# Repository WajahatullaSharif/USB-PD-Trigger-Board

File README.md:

# **USB C PD Trigger Board**
- The USB PD Trigger Board is based on **AP33771C USB PD3.1 ERP sink controller** from Diodes Incorporated. 
- This board negotiates required **voltages (5V/9V/12V/15V/20V/28V) and current (0 to 5A max)** profiles requested using the respective jumpers with the Type C Power Source (typically charger/adaptor). 
- It includes safety features like Over/Under Voltage, Over Current, Over Temperature Protections along with IN/OUT isolation. The board is also immune to ± 30 kV Air/Contact ESD dicharge (IEC 61000-4-2)

# Kicad 9 files
- The hardware is designed on KiCad 9.
## Schematic

## Layout

## 3D Model

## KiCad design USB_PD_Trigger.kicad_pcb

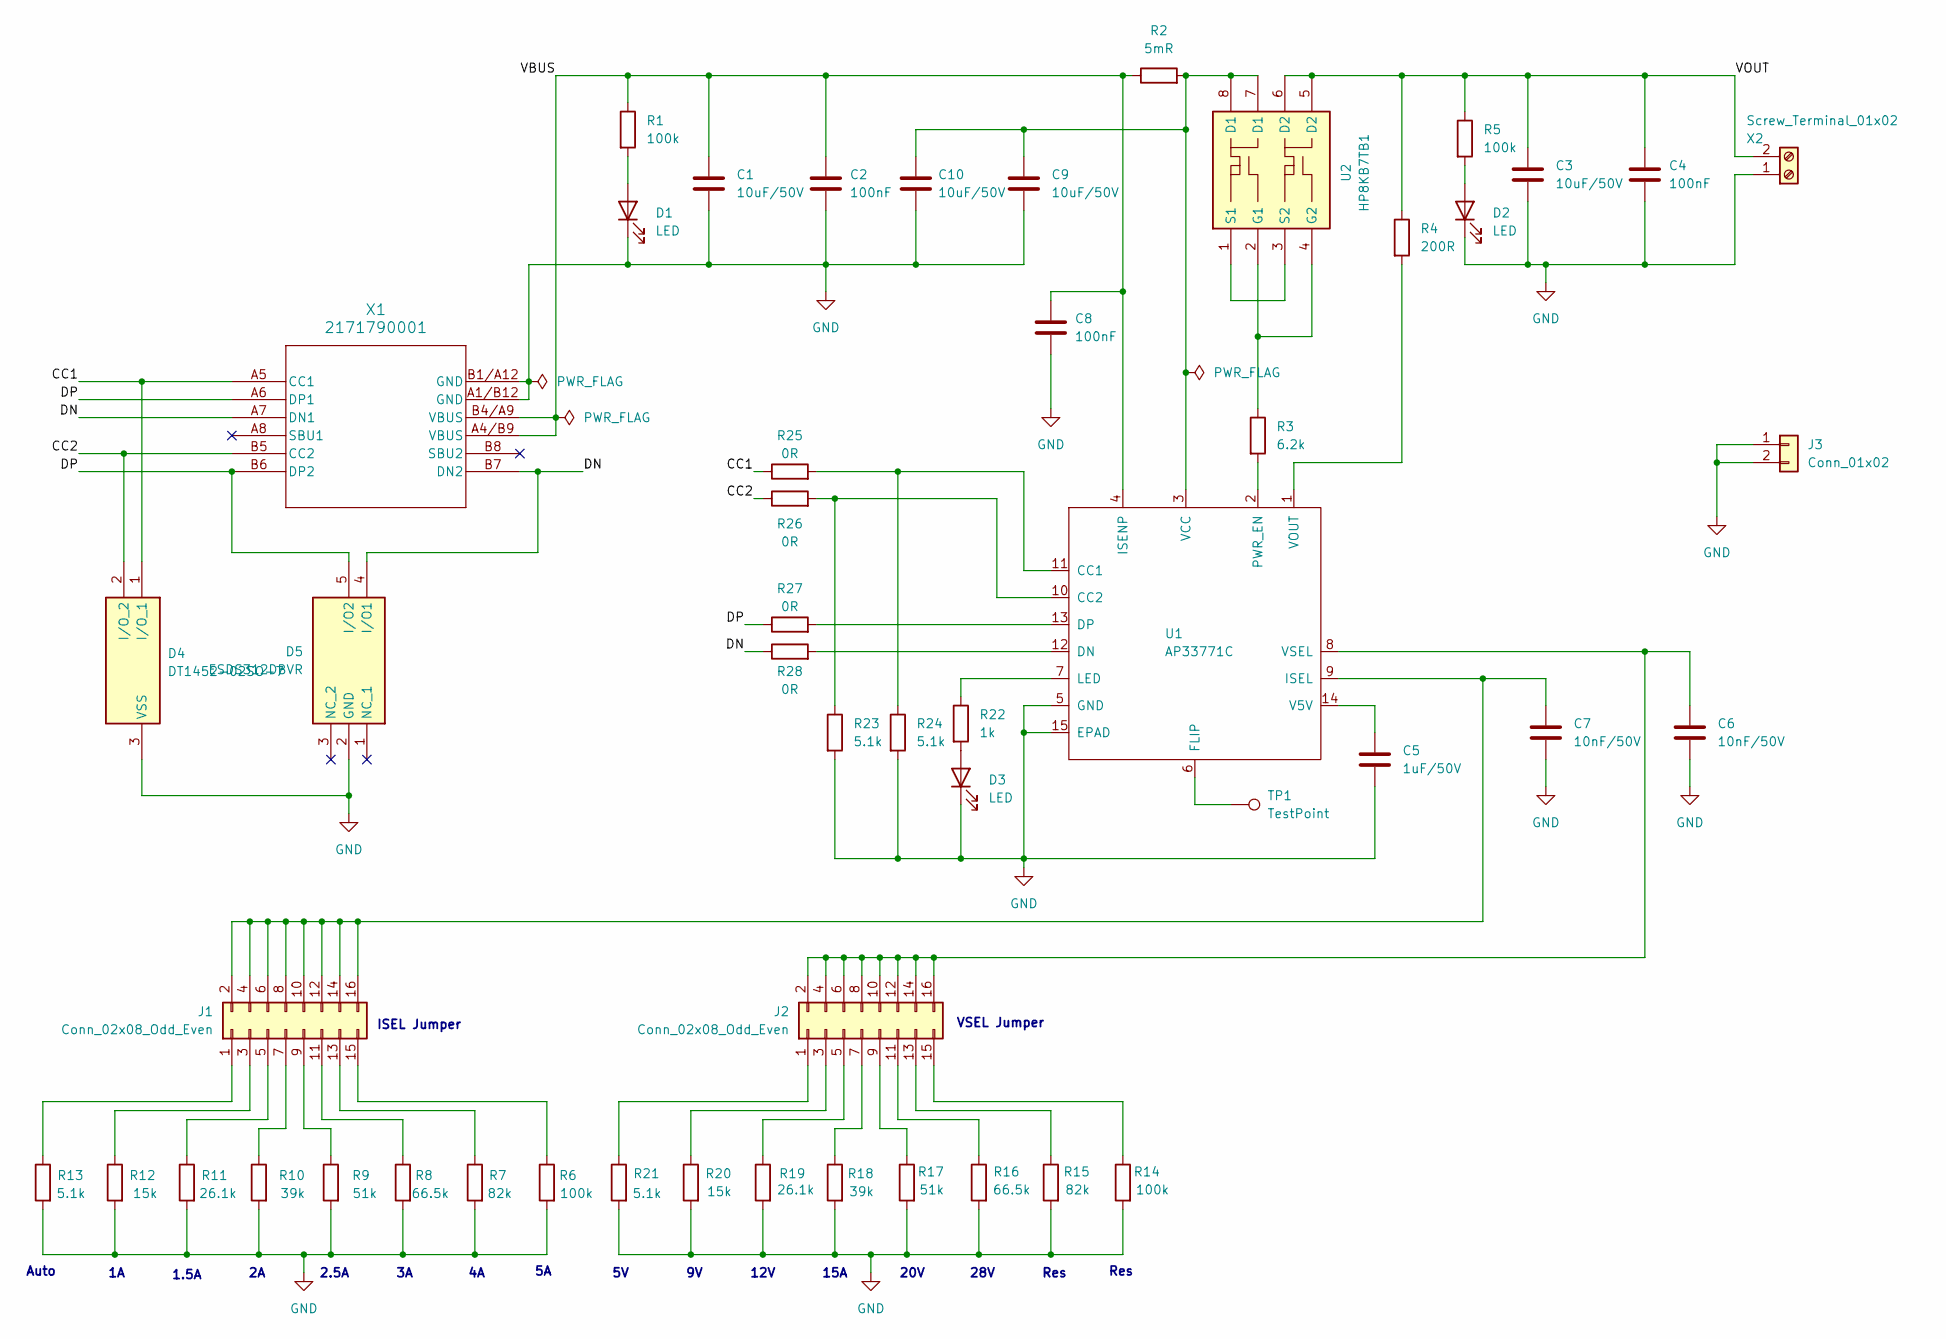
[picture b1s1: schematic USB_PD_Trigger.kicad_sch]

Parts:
C1, C3, C9, C10: 10uF/50V; C_1206_3216Metric; Manufacturer_Part_Number CL31B106KBHNNNE
C2, C4, C8: 100nF; C_0603_1608Metric; Manufacturer_Part_Number GRM188R71H104KA93D
C5: 1uF/50V; C_0603_1608Metric; Manufacturer_Part_Number CC0603KRX7R9BB105
C6, C7: 10nF/50V; C_0603_1608Metric; Manufacturer_Part_Number CC0603KRX7R9BB103
D1, D2, D3: LED; LED_0805_2012Metric
D4: DT1452-02SO-7; Mouser Part Number 621-DT1452-02SO-7
D5: ESDS312DBVR; Mouser Part Number 595-ESDS312DBVR
J1, J2: Conn_02x08_Odd_Even; PinHeader_2x08_P2.54mm_Vertical
J3: Conn_01x02; PinHeader_1x02_P2.54mm_Vertical
R1, R5, R6, R14: 100k; R_0603_1608Metric
R2: 5mR; R_1206_3216Metric
R3: 6.2k; R_0603_1608Metric
R4: 200R; R_0603_1608Metric
R7, R15: 82k; R_0603_1608Metric
R8, R16: 66.5k; R_0603_1608Metric
R9, R17: 51k; R_0603_1608Metric
R10, R18: 39k; R_0603_1608Metric
R11, R19: 26.1k; R_0603_1608Metric
R12, R20: 15k; R_0603_1608Metric
R13, R21, R23, R24: 5.1k; R_0603_1608Metric
R22: 1k; R_0603_1608Metric
R25, R26, R27, R28: 0R; R_0603_1608Metric
TP1: TestPoint; TestPoint_Keystone_5000-5004_Miniature
U1: AP33771C; AP33771CFBZ13FA01
U2: HP8KB7TB1; Manufacturer_Part_Number HP8KB7TB1
X1: 2171790001; 2171790001_MOL
X2: Screw_Terminal_01x02; TerminalBlock_Phoenix_MKDS-1,5-2_1x02_P5.00mm_Horizontal

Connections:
/CC1: D4.1 (I/O_1), R25.1, X1.A5 (CC1)
/CC2: D4.2 (I/O_2), R26.1, X1.B5 (CC2)
/DN: D5.4 (I/O1), R28.1, X1.A7 (DN1), X1.B7 (DN2)
/DP: D5.5 (I/O2), R27.1, X1.A6 (DP1), X1.B6 (DP2)
/VBUS: C1.1, C2.1, C8.1, R1.1, R2.1, U1.4 (ISENP), X1.A4/B9 (VBUS), X1.B4/A9 (VBUS)
/VOUT: C3.1, C4.1, R4.1, R5.1, U2.5 (D2), U2.6 (D2), U2.11, U2.12, X2.2
GND: C1.2, C2.2, C3.2, C4.2, C5.2, C6.2, C7.2, C8.2, C9.2, C10.2, D1.1 (K), D2.1 (K), D3.1 (K), D4.3 (VSS), D5.1 (NC_1), D5.2 (GND), D5.3 (NC_2), J3.1, J3.2, R6.2, R7.2, R8.2, R9.2, R10.2, R11.2, R12.2, R13.2, R14.2, R15.2, R16.2, R17.2, R18.2, R19.2, R20.2, R21.2, R23.2, R24.2, U1.5 (GND), U1.15 (EPAD), X1.A1/B12 (GND), X1.B1/A12 (GND), X2.1
unnamed: D1.2 (A), R1.2
unnamed: D2.2 (A), R5.2
unnamed: D3.2 (A), R22.2
unnamed: J1.1, R13.1
unnamed: J1.3, R12.1
unnamed: J1.5, R11.1
unnamed: J1.7, R10.1
unnamed: J1.9, R9.1
unnamed: C7.1, J1.2, J1.4, J1.6, J1.8, J1.10, J1.12, J1.14, J1.16, U1.9 (ISEL)
unnamed: J1.11, R8.1
unnamed: J1.13, R7.1
unnamed: J1.15, R6.1
unnamed: J2.1, R21.1
unnamed: J2.3, R20.1
unnamed: J2.5, R19.1
unnamed: J2.7, R18.1
unnamed: J2.9, R17.1
unnamed: C6.1, J2.2, J2.4, J2.6, J2.8, J2.10, J2.12, J2.14, J2.16, U1.8 (VSEL)
unnamed: J2.11, R16.1
unnamed: J2.13, R15.1
unnamed: J2.15, R14.1
unnamed: R24.1, R25.2, U1.11 (CC1)
unnamed: R23.1, R26.2, U1.10 (CC2)
unnamed: R28.2, U1.12 (DN)
unnamed: R27.2, U1.13 (DP)
unnamed: TP1.1, U1.6 (FLIP)
unnamed: R22.1, U1.7 (LED)
unnamed: R3.2, U1.2 (PWR_EN)
unnamed: C5.1, U1.14 (V5V)
unnamed: C9.1, C10.1, R2.2, U1.3 (VCC), U2.7 (D1), U2.8 (D1), U2.9, U2.10
unnamed: R4.2, U1.1 (VOUT)
unnamed: R3.1, U2.2 (G1), U2.4 (G2)
unnamed: U2.1 (S1), U2.3 (S2)

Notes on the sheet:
20V
28V
12V
15A
1.5A
ISEL Jumper
Auto
2.5A
Res
VSEL Jumper

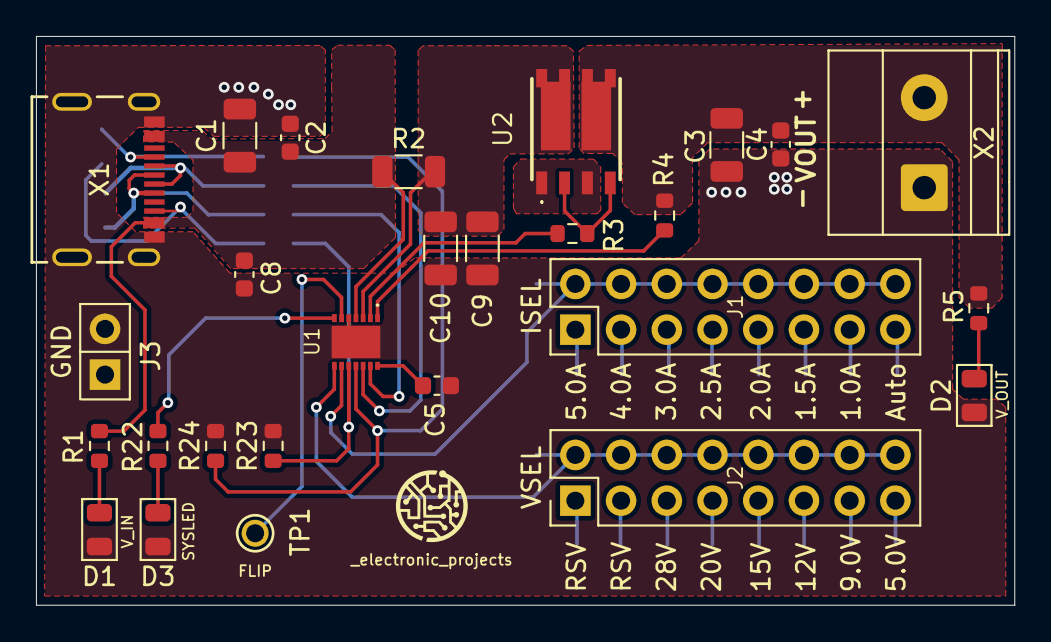
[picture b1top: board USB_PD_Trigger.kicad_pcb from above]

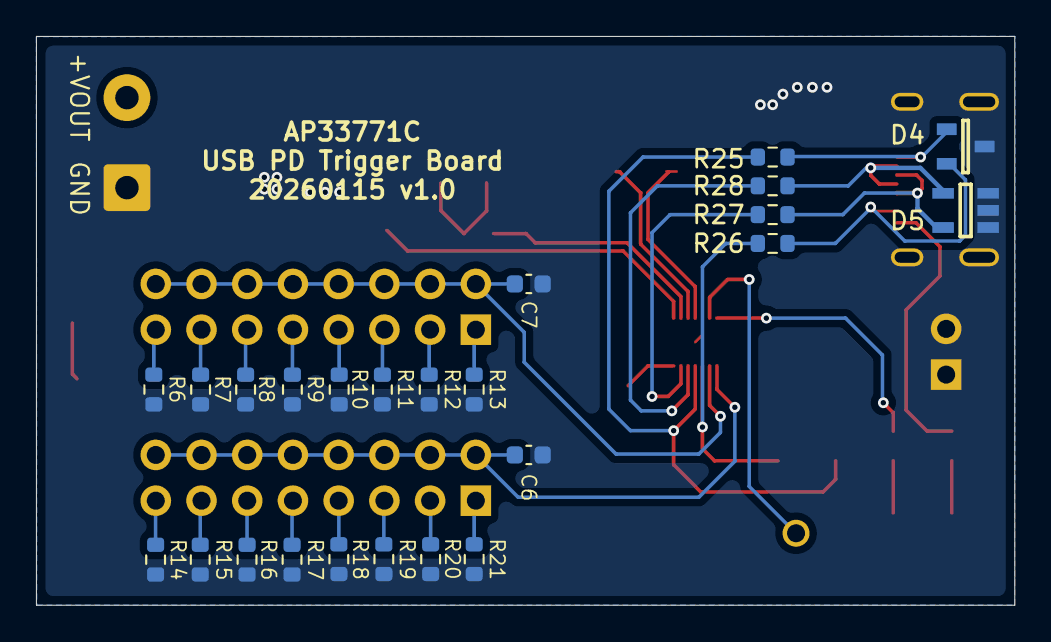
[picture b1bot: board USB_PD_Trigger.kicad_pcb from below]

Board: 2 copper layers, 54.4 x 31.6 mm, 51 parts (24 on the bottom side), 40 nets.

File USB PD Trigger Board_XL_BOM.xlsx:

Sr.No | Ref Des | Qty | Value | MPN | Make | Alternates/Substitutes | Make
1 | C1, C3, C9, C10 | 4 | CER 10UF 50V X7R 1206 | CL31B106KBHNNNE | Samsung Electro-Mechanics
2 | C2, C4, C8 | 3 | CER 100nF ±10% 50V X7R 0603 | GRM188R71H104KA93D | Murata
3 | C5 | 1 | CER 1uF ±10% 50V X7R 0603 | CC0603KRX7R9BB105 | YAGEO
4 | C6, C7 | 2 | CER 10nF ±10% 50V X7R 0603 | CC0603KRX7R9BB103 | YAGEO
5 | D1 | 1 | 0805 GREEN SMD LED | APT2012CGCK | Kingbright
6 | D2 | 1 | 0805 BLUE SMD LED | APT2012LVBC/D | Kingbright
7 | D3 | 1 | 0805 ORANGE SMD LED | APT2012SECK/J4-PRV | Kingbright
8 | D4, D5 | 2 | TVS DIODE 5.5VWM 7.6VC 2X2SON | ESD441DPLR | Texas Instruments
9 | D5, D6 | 2 | TVS DIODE 3.6VWM 6.8VC 2X1SON | ESD321DPYR | Texas Instruments
10 | U1 | 1 | USB EXT POWER RANGE W-DFN3030-14 | AP33771CFBZ-13-FA01 | Diodes Incorporated
11 | U2 | 1 | 40V 24A, Dual Nch+Nch, HSOP8 | HP8KB7TB1 | ROHM Semiconductor
12 | R1, R5, R6, R14 | 4 | RES 100K OHM 1% 1/10W 0603 | RC0603FR-07100KL | YAGEO
13 | R2 | 1 | RES 5m OHM 1% 1/2W 1206 | PA1206FRF7W0R005L | YAGEO
14 | R3 | 1 | RES 6.2K OHM 5% 1/10W 0603 | RC0603JR-076K2L | YAGEO
15 | R4 | 1 | RES 200Ohms 1/10W 0603 5 % | AF0603JR-07200RL | YAGEO
16 | R7, R15 | 2 | RES 82K OHM 1% 1/10W 0603 | RC0603FR-0782KL | YAGEO
17 | R8, R16 | 2 | RES 66.5K OHM 1% 1/10W 0603 | RC0603FR-0766K5L | YAGEO
18 | R9, R17 | 2 | RES 52.3K OHM 1% 1/10W 0603 | RC0603FR-0752K3L | YAGEO
19 | R10, R18 | 2 | RES 39K OHM 1% 1/10W 0603 | RC0603FR-0739KL | YAGEO
20 | R11, R19 | 2 | RES 26.1K OHM 1% 1/10W 0603 | RC0603FR-0726K1L | YAGEO
21 | R12, R20 | 2 | RES 15K OHM 1% 1/10W 0603 | RC0603FR-0715KL | YAGEO
22 | R13, R21, R23, R24 | 4 | RES 5.1K OHM 1% 1/10W 0603 | RC0603FR-075K1L | YAGEO
23 | R22 | 1 | RES 1K OHM 5% 1/10W 0603 | RC0603JR-071KL | YAGEO
24 | R25, R26, R27, R28 | 4 | RES 0 OHM JUMPER 1/10W 0603 | RC0603JR-070RL | YAGEO
25 | J1, J2 | 2 | Pin Header 16 Position 2.54mm Pitch Dual Row Through Hole -40℃~+105℃ | PZ254V-12-16P | XFCN | 5-146254-4 | TE Connectivity
 |  |  |  |  |  | TSW-108-07-F-D | Samtec Inc.
26 | J3 | 1 | CONN HEADER VERT 2POS 2.54MM | TSW-102-07-F-S | Samtec Inc.
26 | X1 | 1 | CONN RCP USB2.0 TYP C 24P SMD RA | 2171790001 | Molex
27 | X2 | 1 | 2 Position Wire to Board Terminal Block Through Hole 5mm | KF301-5.0-2P | Cixi Kefa Elec | TB002-500-02BE | Same Sky
 |  |  |  |  |  | 691137710002 | Würth Elektronik

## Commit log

2026-01-06 Add KiCad project files
2026-01-06 ISEL1 in Layout
2026-01-06 ISEL in Layout
2026-01-07 Zones completed
2026-01-07 DRC errors resolution
2026-01-08 DRC check complete + gerbers
2026-01-08 Saved PCB Layout
2026-01-08 Gerber pdf generation
2026-01-09 Added sch, layout and 3D images
2026-01-09 Rename image.png to Layout.png
2026-01-14 added stitching vias and changed ESD diodes
2026-01-15 updated schematic and gerbers
2026-01-15 updated BOM with cost
